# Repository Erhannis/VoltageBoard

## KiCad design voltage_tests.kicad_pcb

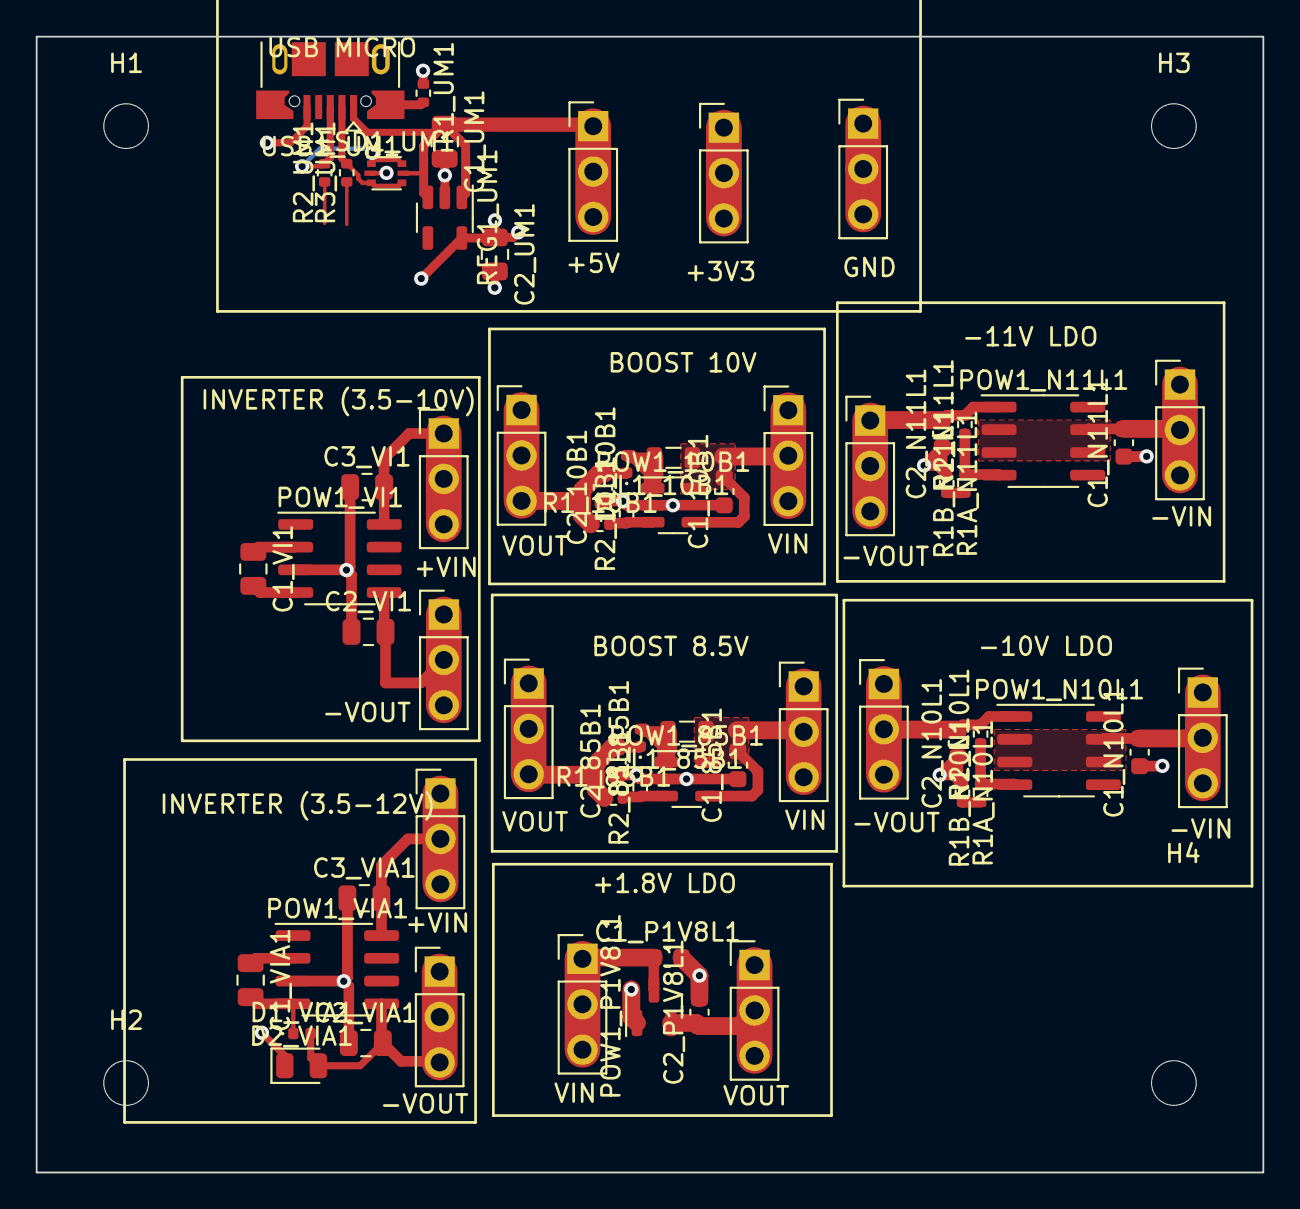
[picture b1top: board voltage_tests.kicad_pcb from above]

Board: 4 copper layers, 68.6 x 63.5 mm, 68 parts (0 on the bottom side), 32 nets.

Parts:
C1_10B1, C1_85B1, C1_N10L1, C1_N11L1, C1_P1V8L1, C2_10B1, C2_85B1, C2_N10L1, C2_N11L1, C2_P1V8L1: 10uF; C_0603_1608Metric
C1_UM1, C1_VI1, C1_VIA1, C2_UM1, C2_VI1, C2_VIA1, C3_VI1, C3_VIA1: 10uF; C_0805_2012Metric
D1_10B1, D1_85B1, D1_VIA1: D_Schottky; D_0402_1005Metric
D2_VIA1: D; D_0805_2012Metric
ESD1_UM1: USBLC6-2P6; SOT-666
H1, H2, H3, H4: MountingHole; MountingHole_2.5mm
J1_3S1, J1_3S2, J1_3S3, J1_3S4, J1_3S5, J1_3S6, J1_3S7, J1_3S8, J1_3S9, J1_3S10, J1_3S11, J1_3S12, J1_3S13, J1_3S14, J1_3S15, J1_3S16, J1_3S17: Conn_01x03_Pin; PinHeader_1x03_P2.54mm_Vertical
L1_10B1, L1_85B1: L 10uH; L_0805_2012Metric
POW1_10B1, POW1_85B1: LM27313XMF; SOT-23-5
POW1_N10L1, POW1_N11L1: LM337L_SO8; SOIC-8_3.9x4.9mm_P1.27mm
POW1_P1V8L1: APE8865N-18-HF-3; SOT-23
POW1_VI1, POW1_VIA1: TC7662Bx0A; SOIC-8_3.9x4.9mm_P1.27mm
R1A_N10L1: R 1.6k 1%; R_0402_1005Metric
R1A_N11L1: R 1.8k 1%; R_0402_1005Metric
R1B_N10L1, R1B_N11L1: R 75 1%; R_0402_1005Metric
R1_10B1, R1_85B1: R 100k 1%; R_0402_1005Metric
R1_UM1: 1M; R_0402_1005Metric
R2_10B1: R 14k 1%; R_0402_1005Metric
R2_85B1: R 16k 1%; R_0402_1005Metric
R2_N10L1, R2_N11L1: R 240 1%; R_0402_1005Metric
R2_UM1, R3_UM1: 27; R_0402_1005Metric
REG1_UM1: AP2112K-3.3; SOT-23-5
USB1_UM1: USB_B_Micro; USB_Micro-B_XKB_U254-051T-4BH83-F1S

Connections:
+3V3: C2_UM1.1, J1_3S2.1, J1_3S2.2, J1_3S2.3, REG1_UM1.5 (VOUT)
/DC Boost 8.5v/VIN: C1_85B1.2, J1_3S15.1, J1_3S15.2, J1_3S15.3, L1_85B1.1, POW1_85B1.4 (EN), POW1_85B1.5 (VIN)
/DC Boost 8.5v/VOUT: C2_85B1.2, D1_85B1.1 (K), J1_3S14.1, J1_3S14.2, J1_3S14.3, R1_85B1.1
/DC Boost 10v/VIN: C1_10B1.2, J1_3S13.1, J1_3S13.2, J1_3S13.3, L1_10B1.1, POW1_10B1.4 (EN), POW1_10B1.5 (VIN)
/DC Boost 10v/VOUT: C2_10B1.2, D1_10B1.1 (K), J1_3S12.1, J1_3S12.2, J1_3S12.3, R1_10B1.1
/Negative LDO -10v/-VIN: C1_N10L1.2, J1_3S11.1, J1_3S11.2, J1_3S11.3, POW1_N10L1.2 (VI), POW1_N10L1.3 (VI), POW1_N10L1.6 (VI), POW1_N10L1.7 (VI)
/Negative LDO -10v/-VOUT: C2_N10L1.2, J1_3S10.1, J1_3S10.2, J1_3S10.3, POW1_N10L1.1 (VO), R2_N10L1.2
/Negative LDO -11v/-VIN: C1_N11L1.2, J1_3S9.1, J1_3S9.2, J1_3S9.3, POW1_N11L1.2 (VI), POW1_N11L1.3 (VI), POW1_N11L1.6 (VI), POW1_N11L1.7 (VI)
/Negative LDO -11v/-VOUT: C2_N11L1.2, J1_3S8.1, J1_3S8.2, J1_3S8.3, POW1_N11L1.1 (VO), R2_N11L1.2
/Positive LDO +1.8v/VIN: C1_P1V8L1.1, J1_3S16.1, J1_3S16.2, J1_3S16.3, POW1_P1V8L1.3 (VI)
/Positive LDO +1.8v/VOUT: C2_P1V8L1.1, J1_3S17.1, J1_3S17.2, J1_3S17.3, POW1_P1V8L1.2 (VO)
/Splitter(3)3/IN: C3_VI1.2, J1_3S4.1, J1_3S4.2, J1_3S4.3, POW1_VI1.8 (V+)
/Splitter(3)4/IN: C3_VIA1.2, J1_3S5.1, J1_3S5.2, J1_3S5.3, POW1_VIA1.8 (V+)
/Splitter(3)5/IN: C2_VI1.2, J1_3S6.1, J1_3S6.2, J1_3S6.3, POW1_VI1.5 (VOUT)
/Splitter(3)6/IN: C2_VIA1.2, D1_VIA1.2 (A), D2_VIA1.2 (A), J1_3S7.1, J1_3S7.2, J1_3S7.3, POW1_VIA1.5 (VOUT)
/Splitter(3)/IN: C1_UM1.1, ESD1_UM1.5 (VBUS), J1_3S1.1, J1_3S1.2, J1_3S1.3, REG1_UM1.1 (VIN), REG1_UM1.3 (EN), USB1_UM1.1 (VBUS)
GND: C1_10B1.1, C1_85B1.1, C1_N10L1.1, C1_N11L1.1, C1_P1V8L1.2, C1_UM1.2, C2_10B1.1, C2_85B1.1, C2_N10L1.1, C2_N11L1.1, C2_P1V8L1.2, C2_UM1.2, C2_VI1.1, C2_VIA1.1, C3_VI1.1, C3_VIA1.1, D2_VIA1.1 (K), ESD1_UM1.2 (GND), J1_3S3.1, J1_3S3.2, J1_3S3.3, POW1_10B1.2 (GND), POW1_85B1.2 (GND), POW1_P1V8L1.1 (GND), POW1_VI1.3 (GND), POW1_VIA1.3 (GND), R1A_N10L1.1, R1A_N11L1.1, R1_UM1.1, R2_10B1.2, R2_85B1.2, REG1_UM1.2 (GND), USB1_UM1.5 (GND)
unnamed: D1_10B1.2 (A), L1_10B1.2, POW1_10B1.1 (SW)
unnamed: D1_85B1.2 (A), L1_85B1.2, POW1_85B1.1 (SW)
unnamed: C1_VIA1.2, D1_VIA1.1 (K), POW1_VIA1.4 (CAP-)
unnamed: POW1_10B1.3 (FB), R1_10B1.2, R2_10B1.1
unnamed: POW1_85B1.3 (FB), R1_85B1.2, R2_85B1.1
unnamed: POW1_N10L1.4 (ADJ), R1B_N10L1.2, R2_N10L1.1
unnamed: POW1_N11L1.4 (ADJ), R1B_N11L1.2, R2_N11L1.1
unnamed: C1_VI1.1, POW1_VI1.2 (CAP+)
unnamed: C1_VI1.2, POW1_VI1.4 (CAP-)
unnamed: C1_VIA1.1, POW1_VIA1.2 (CAP+)
unnamed: R1A_N10L1.2, R1B_N10L1.1
unnamed: R1A_N11L1.2, R1B_N11L1.1
unnamed: ESD1_UM1.1 (I/O1), ESD1_UM1.6 (I/O1), R2_UM1.2, USB1_UM1.3 (D+)
unnamed: ESD1_UM1.3 (I/O2), ESD1_UM1.4 (I/O2), R3_UM1.2, USB1_UM1.2 (D-)
unnamed: R1_UM1.2, USB1_UM1.6 (Shield)

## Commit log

2023-08-18 Ok! After a long buildup, I think we're off to the races!
2023-08-18 Ok, I've added all the power chips and splitters; that MAY be it
2023-08-18 Ok, maybe that's everything?
2023-08-18 Ok, added an 1v8 LDO *sigh*
2023-08-18 AND the labels
2023-08-18 Hash, and gerbers
2023-08-18 Eh, moved repo
